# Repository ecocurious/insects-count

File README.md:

## Insektencounter
Ziel dieses Projekts ist die Entwicklung eines Geräts zur Erkennung und Zählung verschiedener Insektenarten.
Damit soll es dann möglich sein, die Artenvielfalt und deren Veränderung engmaschig und lokal zu erfassen. Zusammen mit anderen Umweltdaten kann so eine Karte erstellt werden. 

Dazu wurden zwei Verfahren ausgewählt, um die Insekten erkennen und somit auch zählen zu können.
- optisch mit Hilfe einer Kamera, die Erkennung erfolgt hier mit auf Insekten trainierter KI
- [Erkennung des Flügelschlags mit einem optischen Mikrofon](http://msei.github.io/insects-count/fluegelschlag.html)

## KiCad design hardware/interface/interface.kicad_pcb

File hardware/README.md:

Insect Counter Hardware
=======================

## IR-Transmitter

PCB for modulated IR LED transmitter

## IR-Receiver

PCB to receive modulated IR signal

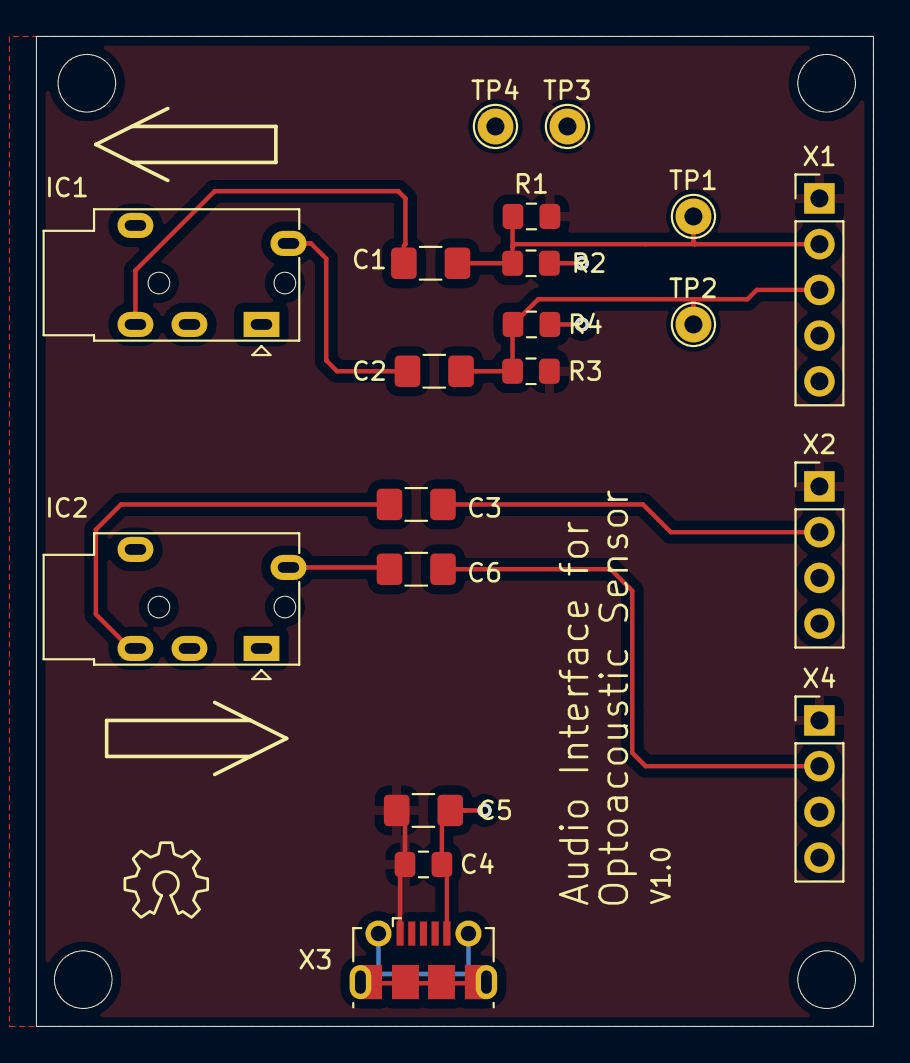
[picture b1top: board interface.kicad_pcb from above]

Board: 2 copper layers, 46.5 x 55.0 mm, 20 parts (0 on the bottom side), 10 nets.

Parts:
C1, C2, C3, C6: 1µF; R_1206_3216Metric_Pad1.42x1.75mm_HandSolder
C4: 100nF; R_0805_2012Metric_Pad1.15x1.40mm_HandSolder
C5: 10µF; R_1206_3216Metric_Pad1.42x1.75mm_HandSolder
IC1, IC2: AudioJackPJ302E; Jack_3.5mm_PJ320E_Horizontal
R1, R2, R3, R4: 10K; R_0805_2012Metric_Pad1.15x1.40mm_HandSolder
TP1, TP2, TP3, TP4: TestPoint; TestPoint_THTPad_D2.0mm_Drill1.0mm
X1: Conn_01x05; PinHeader_1x05_P2.54mm_Vertical
X2, X4: Conn_01x04; PinHeader_1x04_P2.54mm_Vertical
X3: USB_B_Micro; USB_Micro-B_Molex-105017-0001

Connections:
+5V: C4.1, C5.1, R1.1, R3.1, TP3.1, X1.1, X2.1, X3.1, X4.1
GND: C4.2, C5.2, IC1.2, IC2.2, R2.2, R4.2, TP4.1, X1.5, X2.4, X3.5, X4.4
unnamed: C1.1, R1.2, R2.1, TP1.1, X1.2
unnamed: C1.2, IC1.3
unnamed: C2.1, R3.2, R4.1, TP2.1, X1.3
unnamed: C2.2, IC1.4
unnamed: C3.1, X2.2
unnamed: C3.2, IC2.3
unnamed: C6.1, X4.2
unnamed: C6.2, IC2.4

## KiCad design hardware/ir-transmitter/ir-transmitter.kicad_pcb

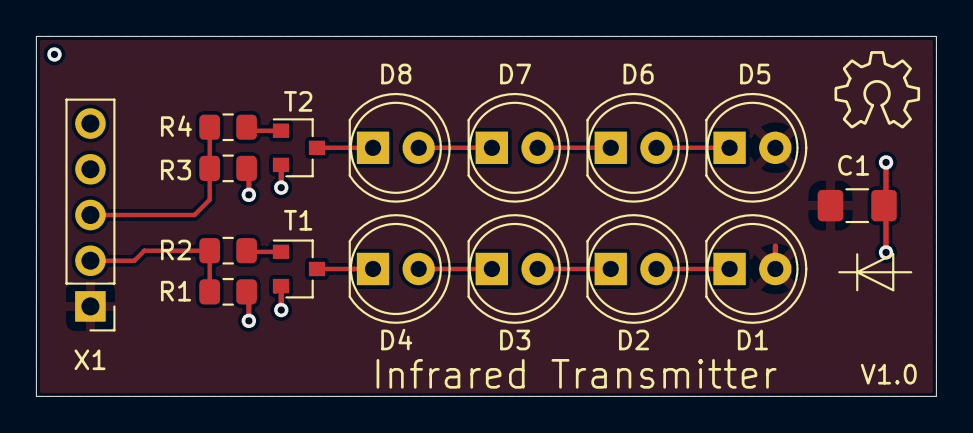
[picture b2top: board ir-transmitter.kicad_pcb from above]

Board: 2 copper layers, 50.0 x 20.0 mm, 16 parts (0 on the bottom side), 14 nets.

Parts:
C1: 10µF; C_1206_3216Metric_Pad1.42x1.75mm_HandSolder
D1, D2, D3, D4, D5, D6, D7, D8: IR333-A; LED_D5.0mm
R1, R3: 10K; R_0805_2012Metric_Pad1.15x1.40mm_HandSolder
R2, R4: 1K; R_0805_2012Metric_Pad1.15x1.40mm_HandSolder
T1, T2: Q_NMOS_GSD; SOT-23
X1: Conn_01x05; PinHeader_1x05_P2.54mm_Vertical

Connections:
+5V: C1.1, D1.2, D5.2, X1.1
GND: C1.2, R1.1, R3.1, T1.2, T2.2, X1.5
unnamed: D1.1, D2.2
unnamed: D2.1, D3.2
unnamed: D3.1, D4.2
unnamed: D4.1, T1.3
unnamed: D5.1, D6.2
unnamed: D6.1, D7.2
unnamed: D7.1, D8.2
unnamed: D8.1, T2.3
unnamed: R1.2, R2.2, X1.2
unnamed: R2.1, T1.1
unnamed: R3.2, R4.2, X1.3
unnamed: R4.1, T2.1

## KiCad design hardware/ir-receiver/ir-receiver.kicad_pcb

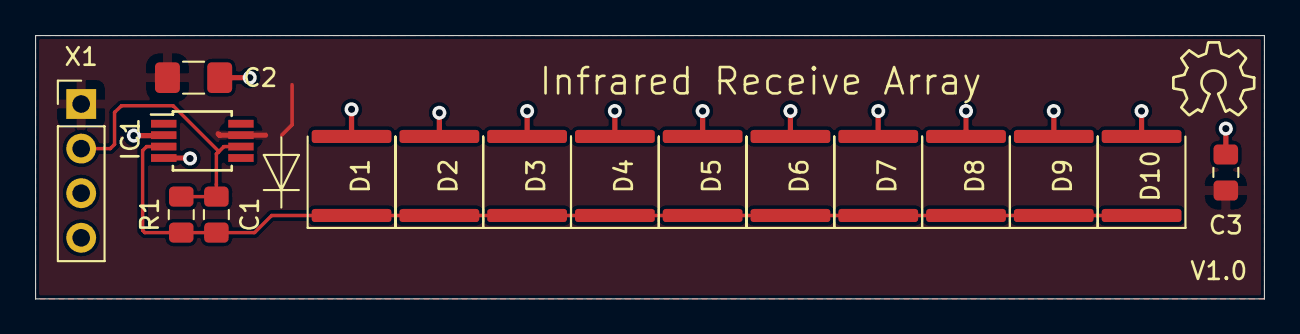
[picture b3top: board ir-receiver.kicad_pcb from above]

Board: 2 copper layers, 70.0 x 15.0 mm, 16 parts (0 on the bottom side), 4 nets.

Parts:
C1: 100pF; C_0805_2012Metric_Pad1.15x1.40mm_HandSolder
C2: 10µF; C_1206_3216Metric_Pad1.42x1.75mm_HandSolder
C3: 100nF; C_0805_2012Metric_Pad1.15x1.40mm_HandSolder
D1, D2, D3, D4, D5, D6, D7, D8, D9, D10: TEMD5080X01; VISHAY-TEMD5080
IC1: OPA381; MSOP-8_3x3mm_P0.65mm
R1: 1,62K; R_0805_2012Metric_Pad1.15x1.40mm_HandSolder
X1: Conn_01x04; PinHeader_1x04_P2.54mm_Vertical

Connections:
+5V: C2.1, C3.1, IC1.7, X1.1
GND: C2.2, C3.2, D1.2, D2.2, D3.2, D4.2, D5.2, D6.2, D7.2, D8.2, D9.2, D10.2, IC1.2, IC1.4, X1.4
unnamed: C1.1, IC1.6, R1.2, X1.2
unnamed: C1.2, D1.1, D2.1, D3.1, D4.1, D5.1, D6.1, D7.1, D8.1, D9.1, D10.1, IC1.3, R1.1

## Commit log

2019-07-02 Initial schematic for IR receiver and transmitter
2019-07-07 Finished layout
2019-07-07 Add layout
2019-07-07 Add gerber
2019-07-07 Add audio interface
2019-07-07 Make receiver PCB two-sided
2019-07-07 Double-sided PCBs
2019-08-20 Add .gitignore
2019-08-20 Create placeholder to add docs directory
2019-08-20 Set theme jekyll-theme-cayman
2019-08-20 Flügelschlagerkennung in den Docs
2019-08-20 Update Readme
    Github project page created, theme selected, project description added
2019-08-20 Moving Readme to github landing page
2019-08-20 Rename landing page so it's covered with the selected theme
2019-08-20 Fix url
2019-08-20 Fix another URL
2019-08-20 Added piCamKI to docs
2019-08-20 Added link to picamki
